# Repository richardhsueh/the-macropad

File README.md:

# The Macropad

## Overview
A custom design Macropad with 9 buttons

## Features
- hot-swappable switches 
- hot-swappable micro controller
- minimal construction for easy repair

## Project Structure
```
project/
├── firmware/          # MCU code if applicable
├── pcb/               # Gerber files for manufacturing the main pcb
└── plate/             # Gerber files for manufacturing the top plate

```

## Requirements
- KiCad 7.0+
- VScode

## Manufacturing
Gerber files are provided in `pcb/` and `plate/`. Recommended fab specs:
- Layers: 2
- Thickness: 1.6mm
- Copper weight: 1oz
- Surface finish: HASL/ENIG

## Assembly

1. Solder the hot-swap sockets to the PCB
2. Insert the switches into the top plate
3. Snap the switches into the hot-swap sockets
4. Insert the microcontroller into the socket
5. Install the spacer and bottom screws
6. Place on the top plate
7. Screw on the top screws

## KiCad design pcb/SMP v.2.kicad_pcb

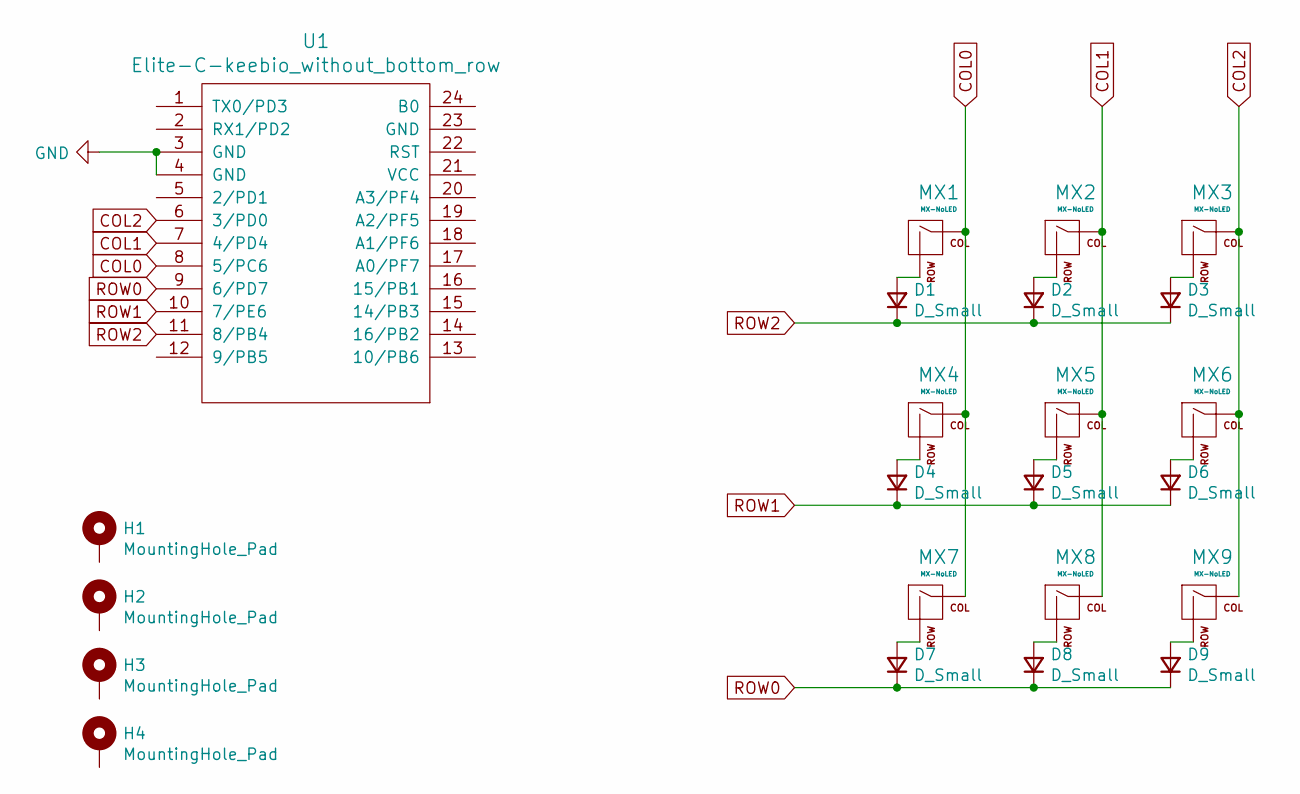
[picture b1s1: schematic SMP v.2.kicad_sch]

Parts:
D1, D2, D3, D4, D5, D6, D7, D8, D9: D_Small; D_DO-35_SOD27_P5.08mm_Horizontal
H1, H2, H3, H4: MountingHole_Pad; MountingHole_3.2mm_M3_Pad
MX1, MX2, MX3, MX4, MX5, MX6, MX7, MX8, MX9: MX-NoLED; MXOnly-1U-NoLED
U1: Elite-C-keebio_without_bottom_row; Elite-C-ZigZag_no-fsilks

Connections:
COL0: MX1.1 (COL), MX4.1 (COL), MX7.1 (COL), U1.8 (5/PC6)
COL1: MX2.1 (COL), MX5.1 (COL), MX8.1 (COL), U1.7 (4/PD4)
COL2: MX3.1 (COL), MX6.1 (COL), MX9.1 (COL), U1.6 (3/PD0)
GND: U1.3 (GND), U1.4 (GND)
unnamed: D1.2 (A), MX1.2 (ROW)
unnamed: D2.2 (A), MX2.2 (ROW)
unnamed: D3.2 (A), MX3.2 (ROW)
unnamed: D4.2 (A), MX4.2 (ROW)
unnamed: D5.2 (A), MX5.2 (ROW)
unnamed: D6.2 (A), MX6.2 (ROW)
unnamed: D7.2 (A), MX7.2 (ROW)
unnamed: D8.2 (A), MX8.2 (ROW)
unnamed: D9.2 (A), MX9.2 (ROW)
ROW0: D1.1 (K), D2.1 (K), D3.1 (K), U1.11 (8/PB4)
ROW1: D4.1 (K), D5.1 (K), D6.1 (K), U1.10 (7/PE6)
ROW2: D7.1 (K), D8.1 (K), D9.1 (K), U1.9 (6/PD7)

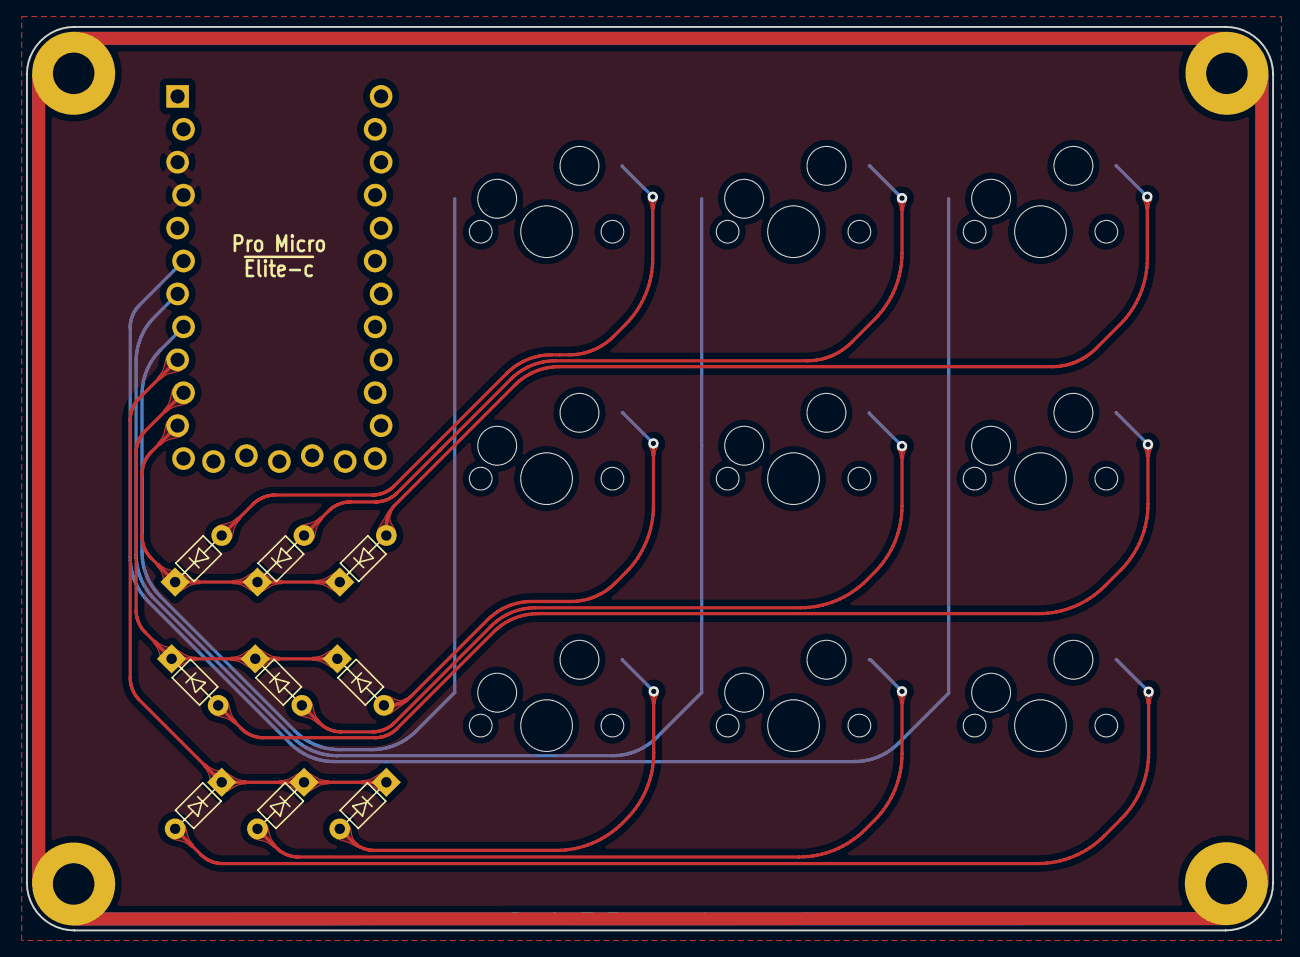
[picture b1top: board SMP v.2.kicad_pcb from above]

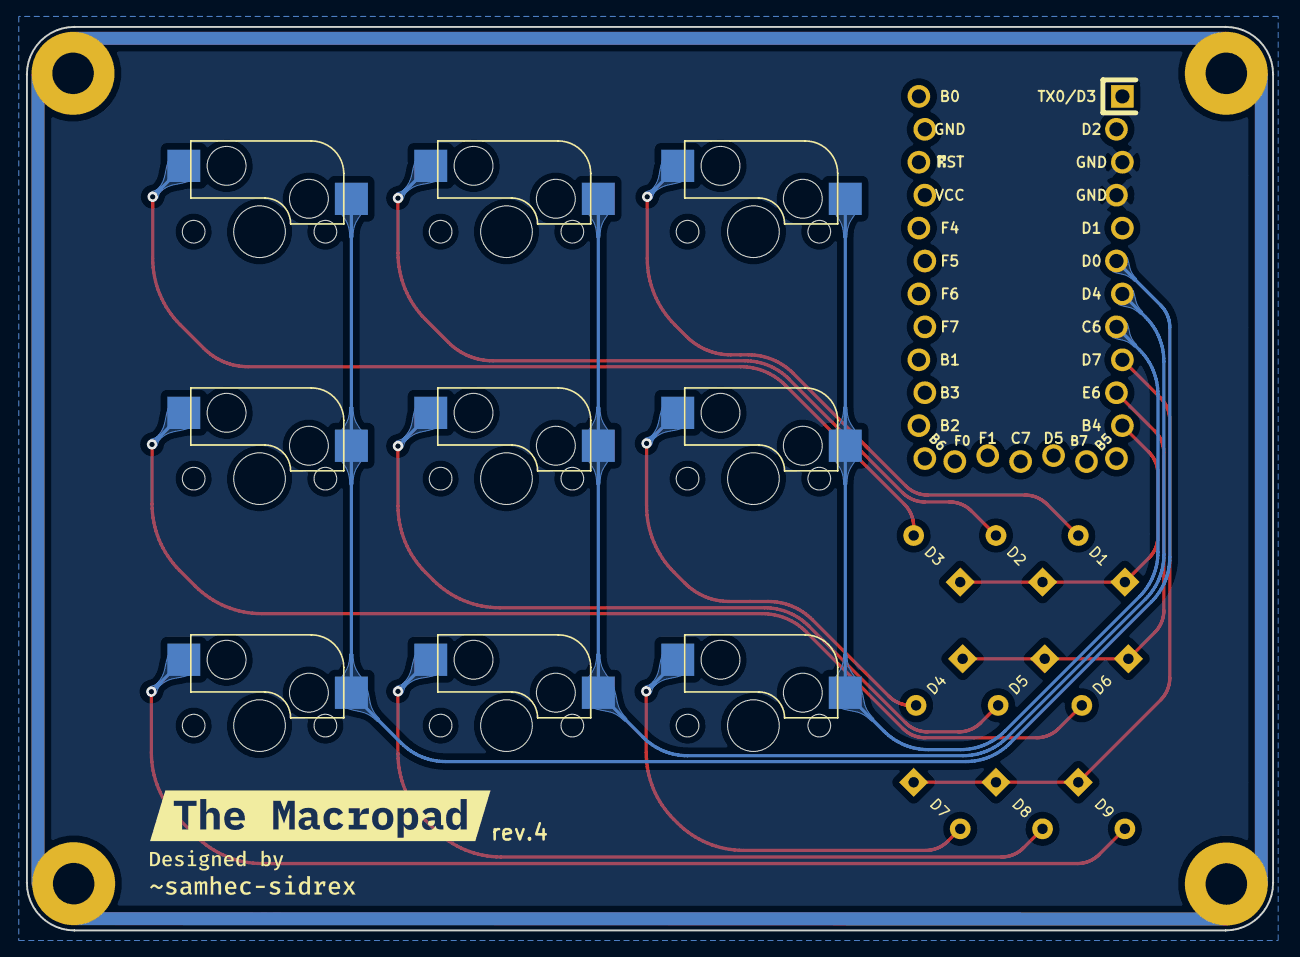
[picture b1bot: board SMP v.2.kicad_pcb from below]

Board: 2 copper layers, 96.1 x 69.7 mm, 26 parts (3 on the bottom side), 16 nets.

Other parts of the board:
kibuzzard-6147B2C4, kibuzzard-6147B3E3, kibuzzard-6147B285: G***; label

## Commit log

2021-08-01 init
2021-08-01 update based on 2moon comment
2021-08-02 include plate and pcb file
2021-08-02 update plate file
2021-08-02 add gerbers
2021-08-18 fine tune top plate after prototype 1
2021-08-19 Add BOM and Pos file
2021-08-22 tidy up the folder
2021-08-25 WIP: on board mcu
2021-08-26 latest version
2021-08-26 update top plate
2021-08-27 refine the routing
2021-08-29 update firmware
2021-08-30 update visual
2021-09-23 pcb and plate finalize for v.4
2021-09-24 last commit
2021-09-29 add top plate
2021-10-01 update firmware and remove top plate
2021-10-06 update pcb sch
2025-02-24 added README and removed outdated data
